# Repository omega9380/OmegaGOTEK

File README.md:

OmegaGOTEK
 - My take on a GOTEK floppy emulator
 - TEST!

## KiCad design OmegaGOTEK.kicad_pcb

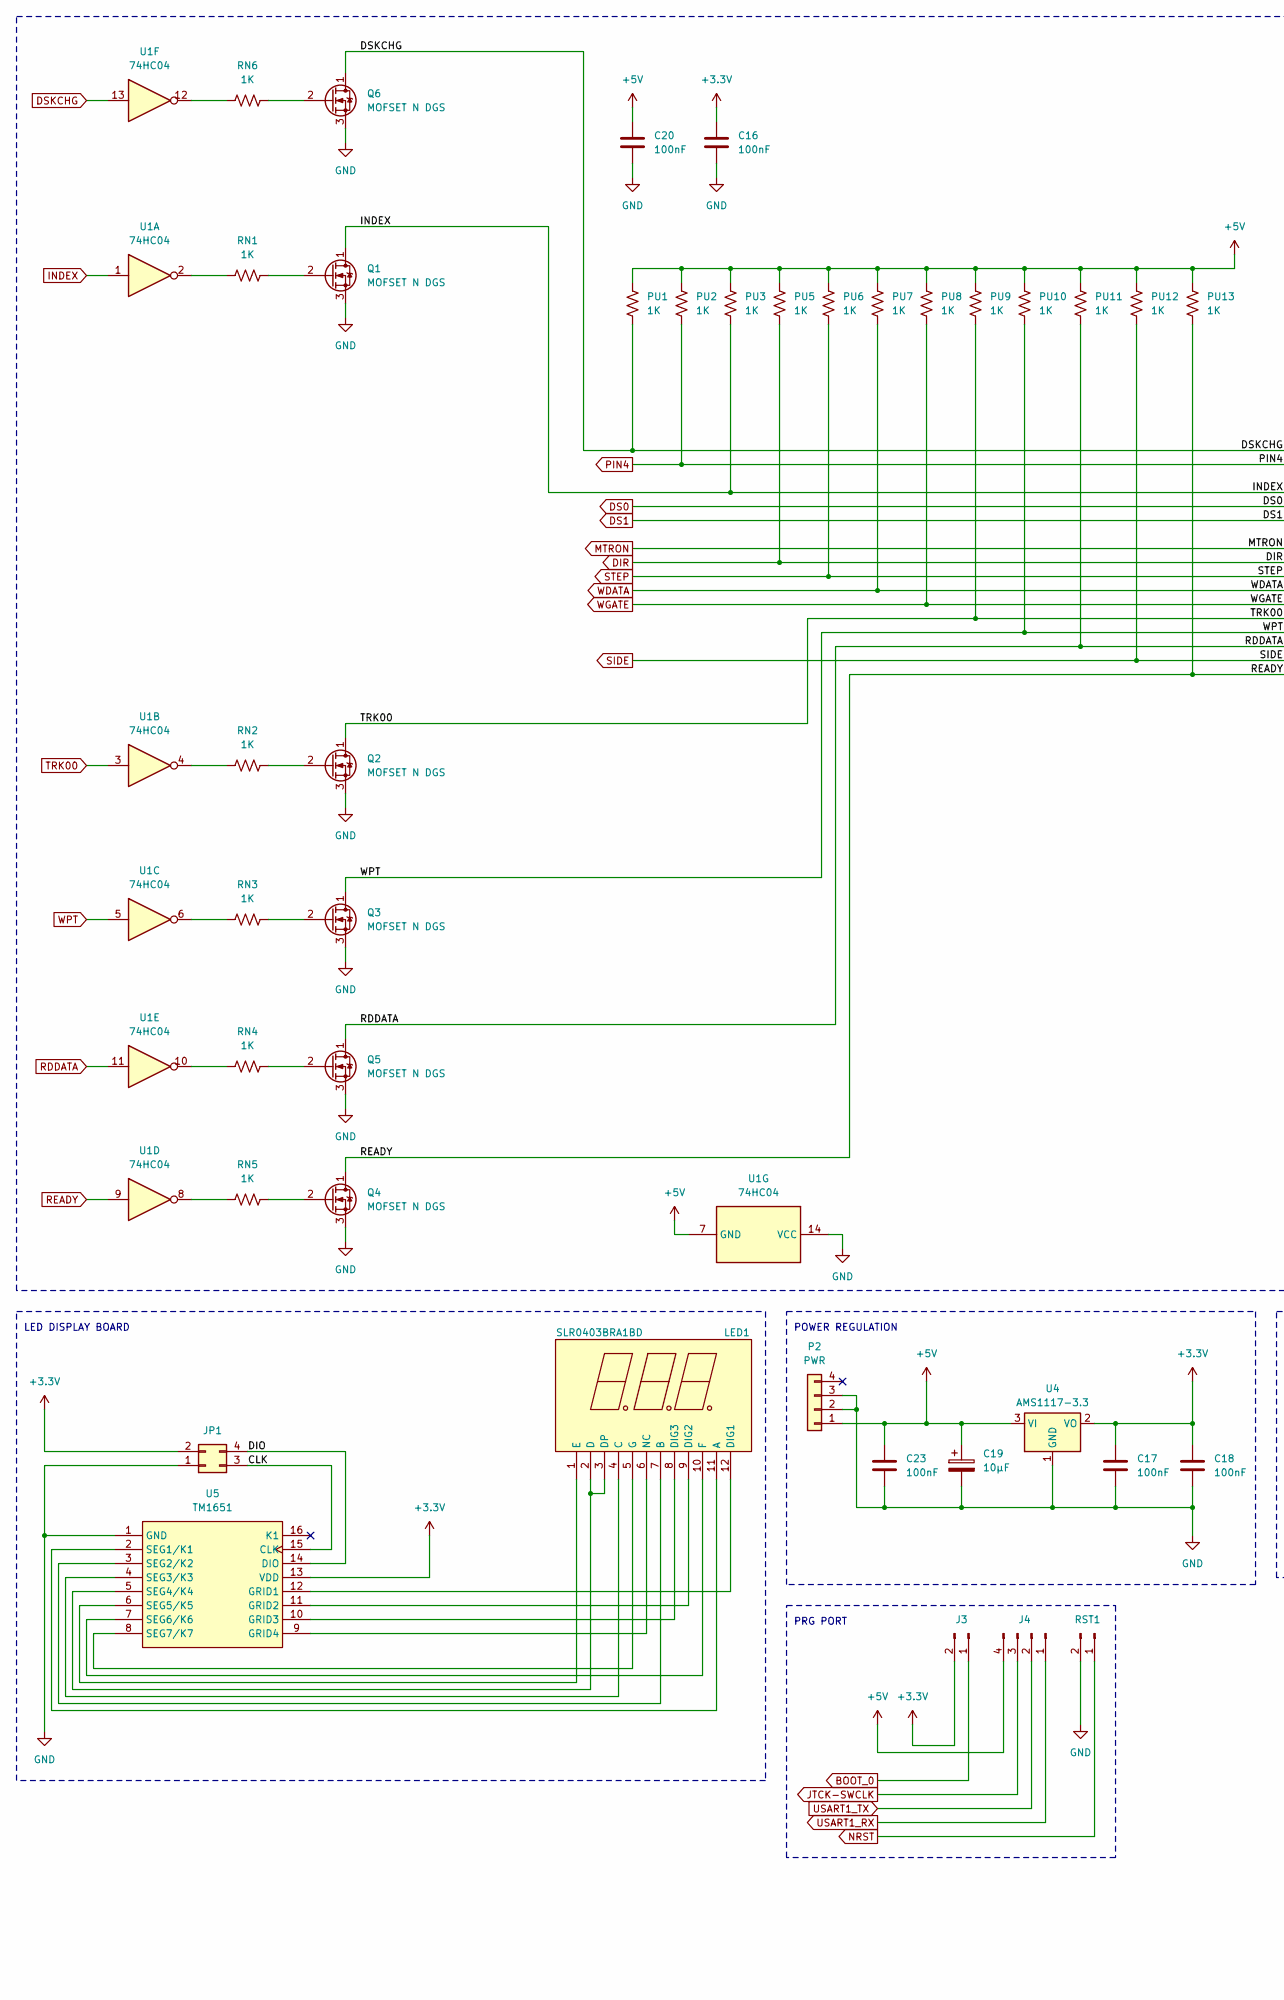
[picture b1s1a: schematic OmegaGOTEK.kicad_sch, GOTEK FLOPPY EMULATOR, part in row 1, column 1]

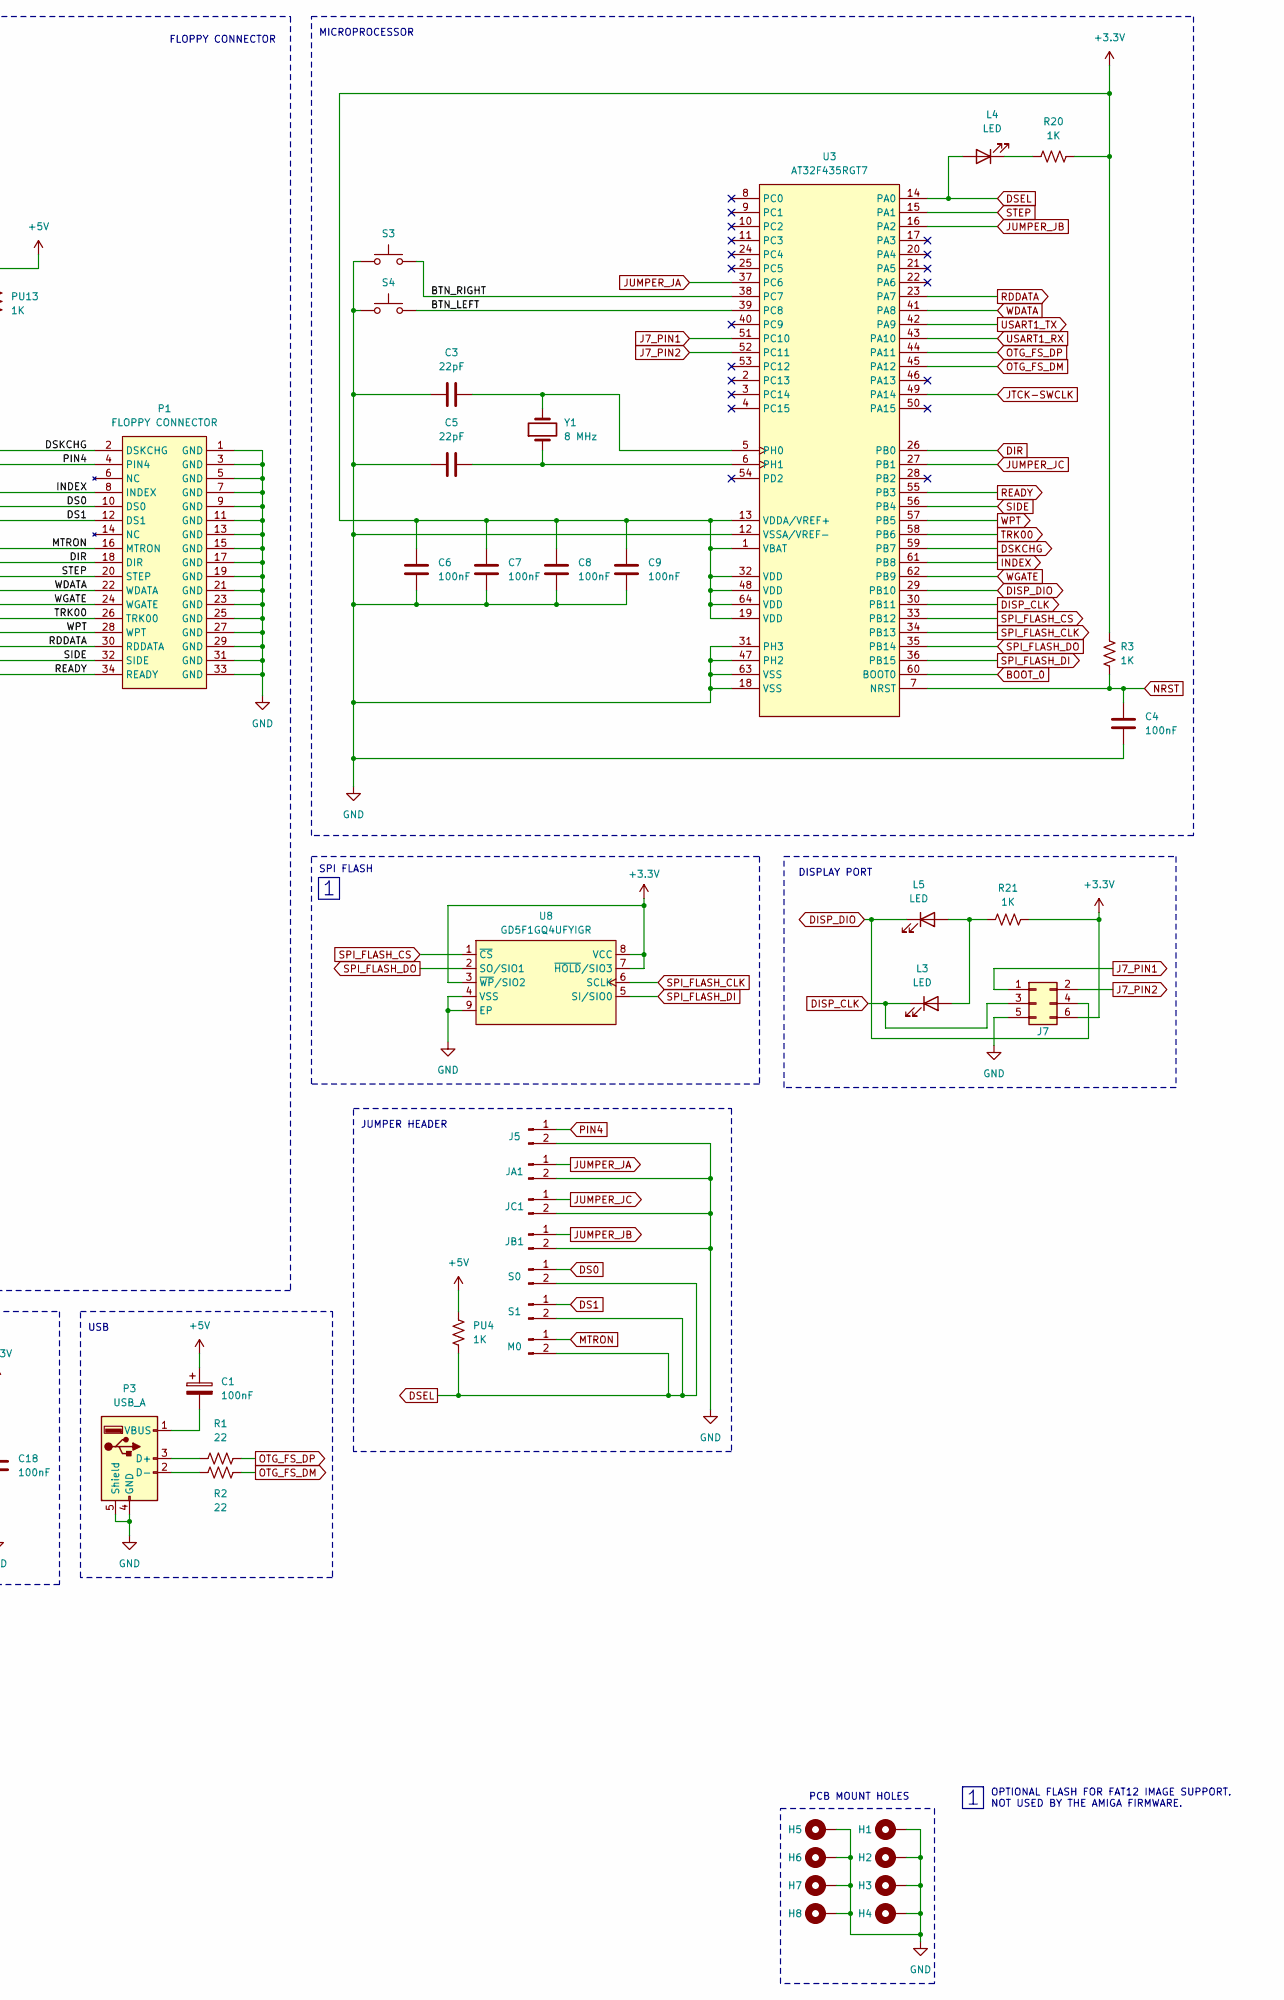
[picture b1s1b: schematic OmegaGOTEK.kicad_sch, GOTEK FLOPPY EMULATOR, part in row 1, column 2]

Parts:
C1: 100nF; CP_Radial_D5.0mm_P2.50mm
C3, C5: 22pF; C_0805_2012Metric_Pad1.18x1.45mm_HandSolder
C4, C6, C7, C8, C9, C16, C17, C18, C20, C23: 100nF; C_0805_2012Metric_Pad1.18x1.45mm_HandSolder
C19: 10µF; CP_Radial_D5.0mm_P2.50mm
H1, H2, H3, H4: MountingHole; MountingHole_3.2mm_M3_Pad_Via
H5, H6, H7, H8: MountingHole; MountingHole_2.2mm_M2_Pad_Via
J3, J5: Conn_01x02_Pin; PinHeader_1x02_P2.54mm_Vertical
J4: Conn_01x04_Pin; PinHeader_2x02_P2.54mm_Vertical
J7: Conn_02x03_Counter_Clockwise; PinHeader_2x03_P2.54mm_Horizontal
JA1: Conn_01x02_Pin; PinHeader_1x02_P2.54mm_Vertical
JB1: Conn_01x02_Pin; PinHeader_1x02_P2.54mm_Vertical
JC1: Conn_01x02_Pin; PinHeader_1x02_P2.54mm_Vertical
JP1: Conn_02x02_Top_Bottom; PinHeader_2x02_P2.54mm_Horizontal
L3, L4, L5: LED; LED_D3.0mm
LED1: SLR0403BRA1BD; LED-SEG-TH_SLR0403BRA1BD; LCSC Part C225910
M0: Conn_01x02_Pin; PinHeader_1x02_P2.54mm_Vertical
P1: FLOPPY CONNECTOR; FloppyHeader_2x17_P2.54mm_Horizontal
P2: PWR; PinHeader_1x04_P2.54mm_Horizontal
P3: USB_A; USB-A-TH_676432911
PU1, PU2, PU3, PU4, PU5, PU6, PU7, PU8, PU9, PU10, PU11, PU12, PU13: 1K; R_0805_2012Metric_Pad1.20x1.40mm_HandSolder
Q1, Q2, Q3, Q4, Q5, Q6: MOFSET N DGS; SOT-23
R1, R2: 22; R_0805_2012Metric_Pad1.20x1.40mm_HandSolder
R3, R20, R21: 1K; R_0805_2012Metric_Pad1.20x1.40mm_HandSolder
RN1, RN2, RN3, RN4, RN5, RN6: 1K; R_0805_2012Metric_Pad1.20x1.40mm_HandSolder
RST1: Conn_01x02_Pin; PinHeader_1x02_P2.54mm_Vertical
S0, S1: Conn_01x02_Pin; PinHeader_1x02_P2.54mm_Vertical
S3, S4: SW_MEC_5E; SW_Tactile_SKHH_Angled
U1: 74HC04; SSOP-14_5.3x6.2mm_P0.65mm
U3: AT32F435RGT7; LQFP-64_L10.0-W10.0-P0.50-LS12.0-BL; LCSC Part C3029577
U4: AMS1117-3.3; SOT-223-3_TabPin2
U5: TM1651; SOIC-16_L9.9-W3.9-P1.27-LS6.0-BL; LCSC Part C40102
U8: GD5F1GQ4UFYIGR; WSON-8_L8.0-W6.0-P1.27-TL-EP; LCSC Part C2986324
Y1: 8 MHz; Crystal_HC49-4H_Vertical

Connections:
+3.3V: C6.1, C7.1, C8.1, C9.1, C16.1, C17.1, C18.1, J3.2, J7.6, JP1.2, R3.2, R20.1, R21.2, U3.1 (VBAT), U3.13 (VDDA/VREF+), U3.19 (VDD), U3.32 (VDD), U3.48 (VDD), U3.64 (VDD), U4.2 (VO), U5.13 (VDD), U8.3 (~WP/SIO2), U8.7 (~HOLD/SIO3), U8.8 (VCC)
+5V: C1.1, C19.1, C20.1, C23.1, J4.4, P2.1, PU1.1, PU2.1, PU3.1, PU4.1, PU5.1, PU6.1, PU7.1, PU8.1, PU9.1, PU10.1, PU11.1, PU12.1, PU13.1, U1.7 (GND), U4.3 (VI)
/BTN_LEFT: S4.2, U3.39 (PC8)
/BTN_RIGHT: S3.2, U3.38 (PC7)
/CLK: JP1.3, U5.15 (CLK)
/DIO: JP1.4, U5.14 (DIO)
BOOT_0: J3.1, U3.60 (BOOT0)
DIR: P1.18 (DIR), PU5.2, U3.26 (PB0)
DISP_CLK: J7.3, L3.1 (K), U3.30 (PB11)
DISP_DIO: J7.4, L5.1 (K), U3.29 (PB10)
DS0: P1.10 (DS0), S0.1
DS1: P1.12 (DS1), S1.1
DSEL: L4.2 (A), M0.2, PU4.2, S0.2, S1.2, U3.14 (PA0)
DSKCHG: P1.2 (DSKCHG), PU1.2, Q6.1 (D), U1.13, U3.59 (PB7)
GND: C3.1, C4.2, C5.1, C6.2, C7.2, C8.2, C9.2, C16.2, C17.2, C18.2, C19.2, C20.2, C23.2, H1.1, H2.1, H3.1, H4.1, H5.1, H6.1, H7.1, H8.1, J5.2, J7.5, JA1.2, JB1.2, JC1.2, JP1.1, P1.1 (GND), P1.3 (GND), P1.5 (GND), P1.7 (GND), P1.9 (GND), P1.11 (GND), P1.13 (GND), P1.15 (GND), P1.17 (GND), P1.19 (GND), P1.21 (GND), P1.23 (GND), P1.25 (GND), P1.27 (GND), P1.29 (GND), P1.31 (GND), P1.33 (GND), P2.2, P2.3, P3.4 (GND), P3.5 (Shield), Q1.3 (S), Q2.3 (S), Q3.3 (S), Q4.3 (S), Q5.3 (S), Q6.3 (S), RST1.2, S3.1, S4.1, U1.14 (VCC), U3.12 (VSSA/VREF-), U3.18 (VSS), U3.31 (PH3), U3.47 (PH2), U3.63 (VSS), U4.1 (GND), U5.1 (GND), U8.4 (VSS), U8.9 (EP)
INDEX: P1.8 (INDEX), PU3.2, Q1.1 (D), U1.1, U3.61 (PB8)
J7_PIN1: J7.1, U3.51 (PC10)
J7_PIN2: J7.2, U3.52 (PC11)
JTCK-SWCLK: J4.3, U3.49 (PA14)
JUMPER_JA: JA1.1, U3.37 (PC6)
JUMPER_JB: JB1.1, U3.16 (PA2)
JUMPER_JC: JC1.1, U3.27 (PB1)
MTRON: M0.1, P1.16 (MTRON)
NRST: C4.1, R3.1, RST1.1, U3.7 (NRST)
unnamed: L3.2 (A), L5.2 (A), R21.1
unnamed: L4.1 (K), R20.2
unnamed: LED1.11 (A), U5.2 (SEG1/K1)
unnamed: LED1.7 (B), U5.3 (SEG2/K2)
unnamed: LED1.4 (C), U5.4 (SEG3/K3)
unnamed: LED1.2 (D), LED1.3 (DP), U5.5 (SEG4/K4)
unnamed: LED1.12 (DIG1), U5.12 (GRID1)
unnamed: LED1.9 (DIG2), U5.11 (GRID2)
unnamed: LED1.8 (DIG3), U5.10 (GRID3)
unnamed: LED1.1 (E), U5.6 (SEG5/K5)
unnamed: LED1.10 (F), U5.7 (SEG6/K6)
unnamed: LED1.5 (G), U5.8 (SEG7/K7)
unnamed: LED1.6 (NC), U5.9 (GRID4)
unnamed: P3.3 (D+), R1.1
unnamed: P3.2 (D-), R2.1
unnamed: C1.2, P3.1 (VBUS)
unnamed: Q1.2 (G), RN1.2
unnamed: Q2.2 (G), RN2.2
unnamed: Q3.2 (G), RN3.2
unnamed: Q4.2 (G), RN5.2
unnamed: Q5.2 (G), RN4.2
unnamed: Q6.2 (G), RN6.2
unnamed: RN1.1, U1.2
unnamed: RN2.1, U1.4
unnamed: RN3.1, U1.6
unnamed: RN4.1, U1.10
unnamed: RN5.1, U1.8
unnamed: RN6.1, U1.12
unnamed: C3.2, U3.5 (PH0), Y1.2
unnamed: C5.2, U3.6 (PH1), Y1.1
OTG_FS_DM: R2.2, U3.45 (PA12)
OTG_FS_DP: R1.2, U3.44 (PA11)
PIN4: J5.1, P1.4 (PIN4), PU2.2
RDDATA: P1.30 (RDDATA), PU11.2, Q5.1 (D), U1.11, U3.23 (PA7)
READY: P1.34 (READY), PU13.2, Q4.1 (D), U1.9, U3.55 (PB3)
SIDE: P1.32 (SIDE), PU12.2, U3.56 (PB4)
SPI_FLASH_CLK: U3.34 (PB13), U8.6 (SCLK)
SPI_FLASH_CS: U3.33 (PB12), U8.1 (~CS)
SPI_FLASH_DI: U3.36 (PB15), U8.5 (SI/SIO0)
SPI_FLASH_DO: U3.35 (PB14), U8.2 (SO/SIO1)
STEP: P1.20 (STEP), PU6.2, U3.15 (PA1)
TRK00: P1.26 (TRK00), PU9.2, Q2.1 (D), U1.3, U3.58 (PB6)
USART1_RX: J4.1, U3.43 (PA10)
USART1_TX: J4.2, U3.42 (PA9)
WDATA: P1.22 (WDATA), PU7.2, U3.41 (PA8)
WGATE: P1.24 (WGATE), PU8.2, U3.62 (PB9)
WPT: P1.28 (WPT), PU10.2, Q3.1 (D), U1.5, U3.57 (PB5)

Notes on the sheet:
MICROPROCESSOR
PCB MOUNT HOLES
PRG PORT
LED DISPLAY BOARD
USB
JUMPER HEADER
SPI FLASH
FLOPPY CONNECTOR
DISPLAY PORT
POWER REGULATION
OPTIONAL FLASH FOR FAT12 IMAGE SUPPORT. NOT USED BY THE AMIGA FIRMWARE.

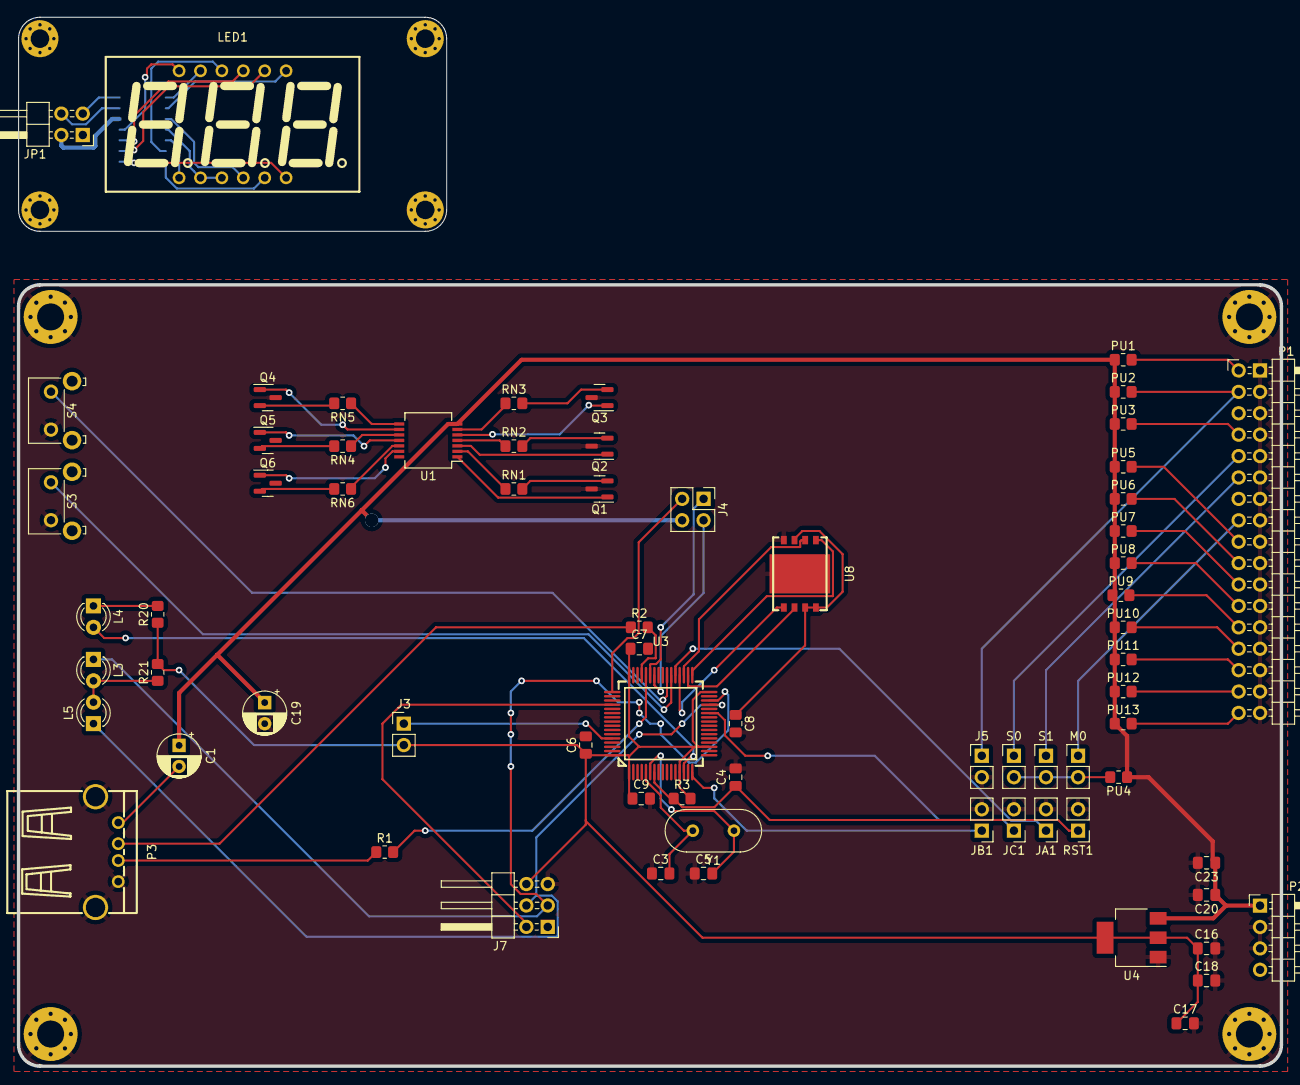
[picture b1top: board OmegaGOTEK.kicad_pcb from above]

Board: 2 copper layers, 149.9 x 92.7 mm, 79 parts (1 on the bottom side), 71 nets.

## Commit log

2023-09-12 second commit
2023-09-13 third commit
2023-09-13 More updates
2023-09-17 Finished schematic
2023-09-17 Started board design
2023-09-17 Just checking
2023-09-20 More board work
